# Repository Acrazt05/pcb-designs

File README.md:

# PCB Designs

Circuit boards I designed for my robotics and embedded projects, in KiCad (plus OmniDrone in Altium). All of them were fabricated, assembled, and brought up working.

| Board | Tool | Key parts |
|---|---|---|
| [ESP32-S3 desk robot](#esp32-s3-desk-robot) | KiCad | ESP32-S3-WROOM-1, 1.69" ST7789 SPI LCD, USB-C, buzzer, push buttons, LDO |
| [ESP32-S3 camera board](#esp32-s3-camera-board) | KiCad | ESP32-S3-WROOM-1, 24-pin camera FPC (IMX219-class sensor), 2.8 V / 1.2 V / 3.3 V rails, LED flash driver, DC jack |
| [Brushless actuator controller](#brushless-actuator-controller) | KiCad | ESP32-C3, DRV8305 three-phase gate driver, six IRF40DM229 MOSFETs, TCAN332 CAN transceiver, AS5600 magnetic encoder, LM75B temperature sensor, LMR14206 buck |
| [OmniDrone](#omnidrone) | Altium | ESP-12 (ESP8266), MPU6050 IMU, HMC5883L magnetometer, MS5611 barometer, TP4056 charger |

Each KiCad folder has the design files (`.kicad_pro`, `.kicad_sch`, `.kicad_pcb`), a `schematic.pdf`, and PNG previews in `images/`. Manufacturer datasheets, 3D models, and vendor footprint libraries are not redistributed here; the symbols and footprints are embedded in the KiCad files.

## ESP32-S3 desk robot
A gift desk robot: an ESP32-S3 drives a color LCD face and a buzzer and reads six buttons, powered over USB-C.

## ESP32-S3 camera board
A camera board for robot vision. It carries the extra 2.8 V and 1.2 V rails the image sensor needs, plus a transistor-switched LED flash.

## Brushless actuator controller
A controller for a humanoid-robot joint: an ESP32-C3 drives a brushless motor through a DRV8305 gate driver and a six-MOSFET three-phase bridge, reads rotor angle from an AS5600 magnetic encoder, monitors temperature, and talks to the rest of the robot over CAN. The design is split into a control board and a power bridge board (separate schematic sheets), with the original single-sheet version kept as `source.kicad_sch`.

## OmniDrone
A mini drone whose frame is the circuit board itself, designed in Altium: ESP-12 Wi-Fi flight computer, IMU, magnetometer and barometer, and onboard LiPo charging. See `omnidrone/` for the schematic and board exports.

---
Vinicio Castillo · [GitHub](https://github.com/Acrazt05) · [LinkedIn](https://www.linkedin.com/in/vinicio-castillo) · [Portfolio](https://github.com/Acrazt05/portfolio)

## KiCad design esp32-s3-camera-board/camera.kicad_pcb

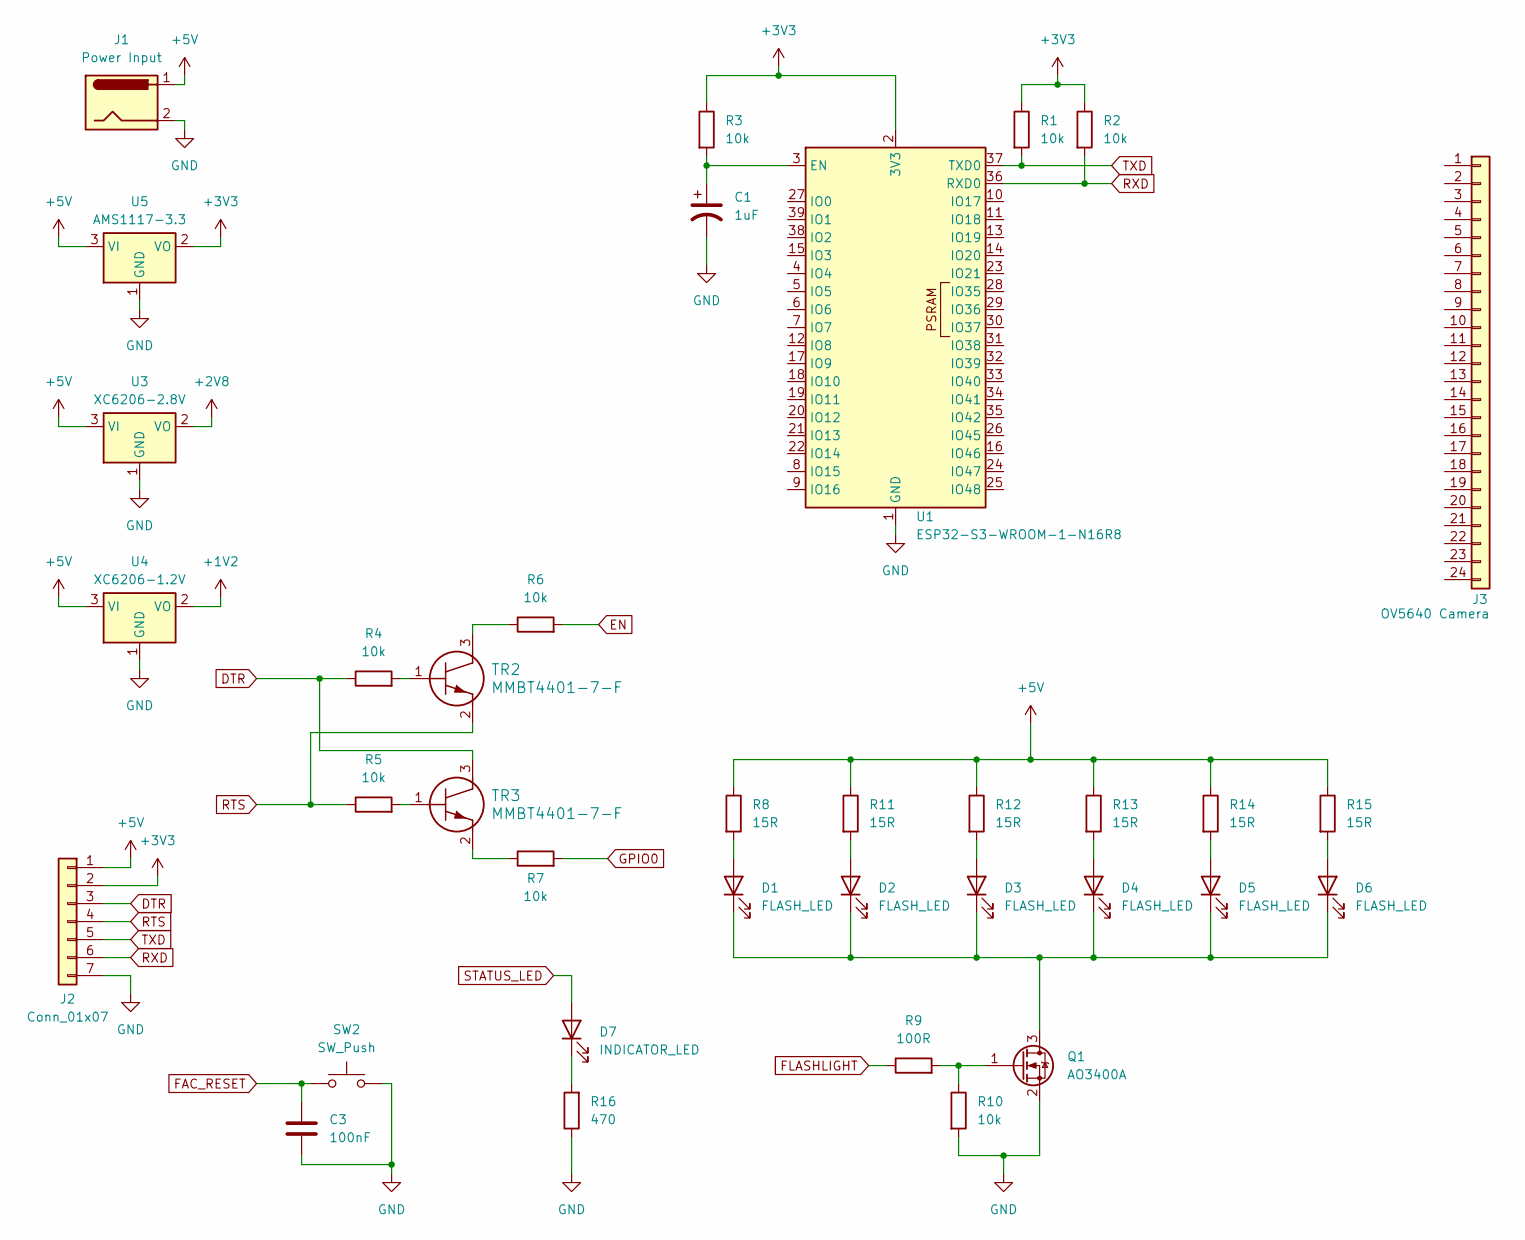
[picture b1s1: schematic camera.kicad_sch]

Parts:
C1: 1uF; CP_Radial_D4.0mm_P2.00mm
C3: 100nF; C_Disc_D5.0mm_W2.5mm_P2.50mm
D1, D2, D3, D4, D5, D6: FLASH_LED; LED_PLCC_2835_Handsoldering
D7: INDICATOR_LED; LED_0603_1608Metric_Pad1.05x0.95mm_HandSolder
J1: Power Input; JACK_ADC-002-x_ADM
J2: Conn_01x07; PinHeader_1x07_P2.54mm_Vertical
J3: OV5640 Camera; XUNPU FPC-05F-24PH20
Q1: AO3400A; SOT-23
R1, R2, R3, R4, R5, R6, R7, R10: 10k; R_1206_3216Metric_Pad1.30x1.75mm_HandSolder
R8, R11, R12, R13, R14, R15: 15R; R_1206_3216Metric_Pad1.30x1.75mm_HandSolder
R9: 100R; R_1206_3216Metric_Pad1.30x1.75mm_HandSolder
R16: 470; R_1206_3216Metric_Pad1.30x1.75mm_HandSolder
SW2: SW_Push; push button 6x6mm 9.5mm height SMD
TR2, TR3: MMBT4401-7-F
U1: ESP32-S3-WROOM-1-N16R8; ESP32-S3-WROOM-1
U3: XC6206-2.8V; SOT-23-3
U4: XC6206-1.2V; SOT-23-3
U5: AMS1117-3.3; SOT-223-3_TabPin2

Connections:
+1V2: U4.2 (VO)
+2V8: U3.2 (VO)
+3V3: J2.2, R1.1, R2.1, R3.1, U1.2 (3V3), U5.2 (VO)
+5V: J1.1, J2.1, R8.1, R11.1, R12.1, R13.1, R14.1, R15.1, U3.3 (VI), U4.3 (VI), U5.3 (VI)
DTR: J2.3, R4.1, TR3.3
EN: R6.2
FAC_RESET: C3.1, SW2.1
FLASHLIGHT: R9.1
GND: C1.2, C3.2, J1.2, J2.7, Q1.2 (S), R10.2, R16.1, SW2.2, U1.1 (GND), U1.40 (GND), U1.41 (GND), U3.1 (GND), U4.1 (GND), U5.1 (GND)
GPIO0: R7.2
unnamed: D1.2 (A), R8.2
unnamed: D1.1 (K), D2.1 (K), D3.1 (K), D4.1 (K), D5.1 (K), D6.1 (K), Q1.3 (D)
unnamed: D2.2 (A), R11.2
unnamed: D3.2 (A), R12.2
unnamed: D4.2 (A), R13.2
unnamed: D5.2 (A), R14.2
unnamed: D6.2 (A), R15.2
unnamed: D7.1 (K), R16.2
unnamed: Q1.1 (G), R9.2, R10.1
unnamed: R4.2, TR2.1
unnamed: R5.2, TR3.1
unnamed: R6.1, TR2.3
unnamed: R7.1, TR3.2
unnamed: C1.1, R3.2, U1.3 (EN)
RTS: J2.4, R5.1, TR2.2
RXD: J2.6, R2.2, U1.36 (RXD0)
STATUS_LED: D7.2 (A)
TXD: J2.5, R1.2, U1.37 (TXD0)

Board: 2 copper layers, 36 parts (0 on the bottom side), 22 nets, no tracks yet.

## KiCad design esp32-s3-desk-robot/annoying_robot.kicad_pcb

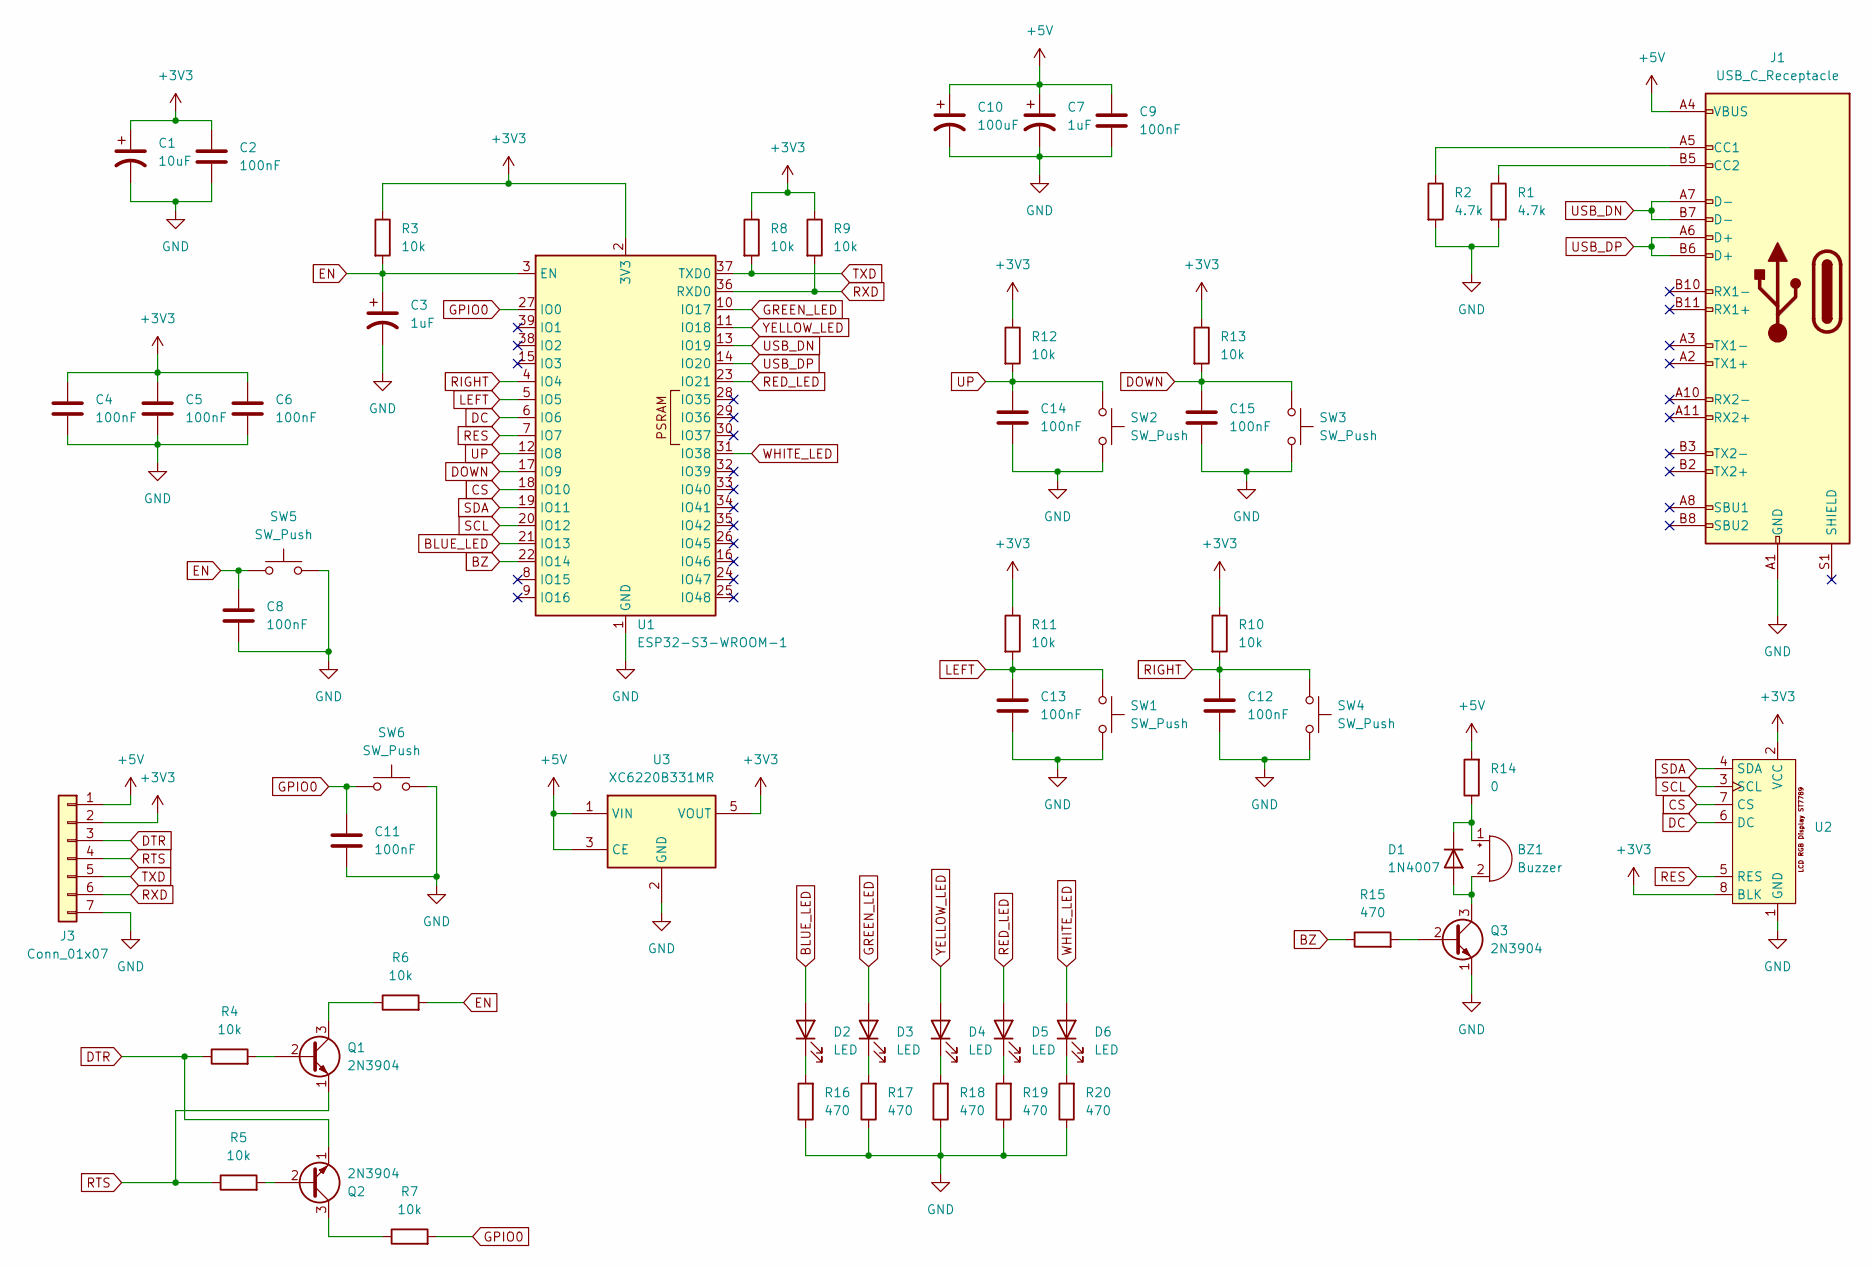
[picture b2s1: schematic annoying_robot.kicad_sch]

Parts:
BZ1: Buzzer; Buzzer_12x9.5RM7.6
C1: 10uF; CP_Radial_D4.0mm_P1.50mm
C2, C4, C5, C6, C8, C9, C11, C12, C13, C14, C15: 100nF; C_Disc_D5.0mm_W2.5mm_P2.50mm
C3, C7: 1uF; CP_Radial_D4.0mm_P2.00mm
C10: 100uF; CP_Radial_D5.0mm_P2.00mm
D1: 1N4007; D_DO-41_SOD81_P10.16mm_Horizontal
D2, D3, D4, D5, D6: LED; LED_D4.0mm
J1: USB_C_Receptacle; USB_C_Receptacle_G-Switch_GT-USB-7010ASV
J3: Conn_01x07; PinHeader_1x07_P2.54mm_Vertical
Q1, Q2, Q3: 2N3904; TO-92
R1, R2: 4.7k; R_1206_3216Metric_Pad1.30x1.75mm_HandSolder
R3, R4, R5, R6, R7, R8, R9, R10, R11, R12, R13: 10k; R_1206_3216Metric_Pad1.30x1.75mm_HandSolder
R14: 0; R_1206_3216Metric_Pad1.30x1.75mm_HandSolder
R15, R16, R17, R18, R19, R20: 470; R_1206_3216Metric_Pad1.30x1.75mm_HandSolder
SW1, SW2, SW3, SW4, SW5, SW6: SW_Push; SW_Push_1P1T_NO_6x6mm_H9.5mm
U1: ESP32-S3-WROOM-1
U2: Screen_1.69_in_240x280_RGB_LCD_3V3_ST7789_SPI_
U3: XC6220B331MR; SOT-23-5

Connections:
+3V3: C1.1, C2.1, C4.1, C5.1, C6.1, J3.2, R3.1, R8.1, R9.1, R10.1, R11.1, R12.1, R13.1, U1.2 (3V3), U2.2 (VCC), U2.8 (BLK), U3.5 (VOUT)
+5V: C7.1, C9.1, C10.1, J1.A4 (VBUS), J1.A9 (VBUS), J1.B4 (VBUS), J1.B9 (VBUS), J3.1, R14.2, U3.1 (VIN), U3.3 (CE)
BLUE_LED: D2.2 (A), U1.21 (IO13)
BZ: R15.1, U1.22 (IO14)
CS: U1.18 (IO10), U2.7 (CS)
DC: U1.6 (IO6), U2.6 (DC)
DOWN: C15.1, R13.2, SW3.1, U1.17 (IO9)
DTR: J3.3, Q2.1 (E), R4.1
EN: C3.1, C8.1, R3.2, R6.2, SW5.1, U1.3 (EN)
GND: C1.2, C2.2, C3.2, C4.2, C5.2, C6.2, C7.2, C8.2, C9.2, C10.2, C11.2, C12.2, C13.2, C14.2, C15.2, J1.A1 (GND), J1.A12 (GND), J1.B1 (GND), J1.B12 (GND), J3.7, Q3.1 (E), R1.2, R2.2, R16.1, R17.1, R18.1, R19.1, R20.1, SW1.2, SW2.2, SW3.2, SW4.2, SW5.2, SW6.2, U1.1 (GND), U1.40 (GND), U1.41 (GND), U2.1 (GND), U3.2 (GND)
GPIO0: C11.1, R7.2, SW6.1, U1.27 (IO0)
GREEN_LED: D3.2 (A), U1.10 (IO17)
LEFT: C13.1, R11.2, SW1.1, U1.5 (IO5)
unnamed: BZ1.1 (+), D1.1 (K), R14.1
unnamed: BZ1.2 (-), D1.2 (A), Q3.3 (C)
unnamed: D2.1 (K), R16.2
unnamed: D3.1 (K), R17.2
unnamed: D4.1 (K), R18.2
unnamed: D5.1 (K), R19.2
unnamed: D6.1 (K), R20.2
unnamed: J1.A5 (CC1), R2.1
unnamed: J1.B5 (CC2), R1.1
unnamed: Q1.2 (B), R4.2
unnamed: Q1.3 (C), R6.1
unnamed: Q2.2 (B), R5.2
unnamed: Q2.3 (C), R7.1
unnamed: Q3.2 (B), R15.2
RED_LED: D5.2 (A), U1.23 (IO21)
RES: U1.7 (IO7), U2.5 (RES)
RIGHT: C12.1, R10.2, SW4.1, U1.4 (IO4)
RTS: J3.4, Q1.1 (E), R5.1
RXD: J3.6, R9.2, U1.36 (RXD0)
SCL: U1.20 (IO12), U2.3 (SCL)
SDA: U1.19 (IO11), U2.4 (SDA)
TXD: J3.5, R8.2, U1.37 (TXD0)
UP: C14.1, R12.2, SW2.1, U1.12 (IO8)
USB_DN: J1.A7 (D-), J1.B7 (D-), U1.13 (IO19)
USB_DP: J1.A6 (D+), J1.B6 (D+), U1.14 (IO20)
WHITE_LED: D6.2 (A), U1.31 (IO38)
YELLOW_LED: D4.2 (A), U1.11 (IO18)

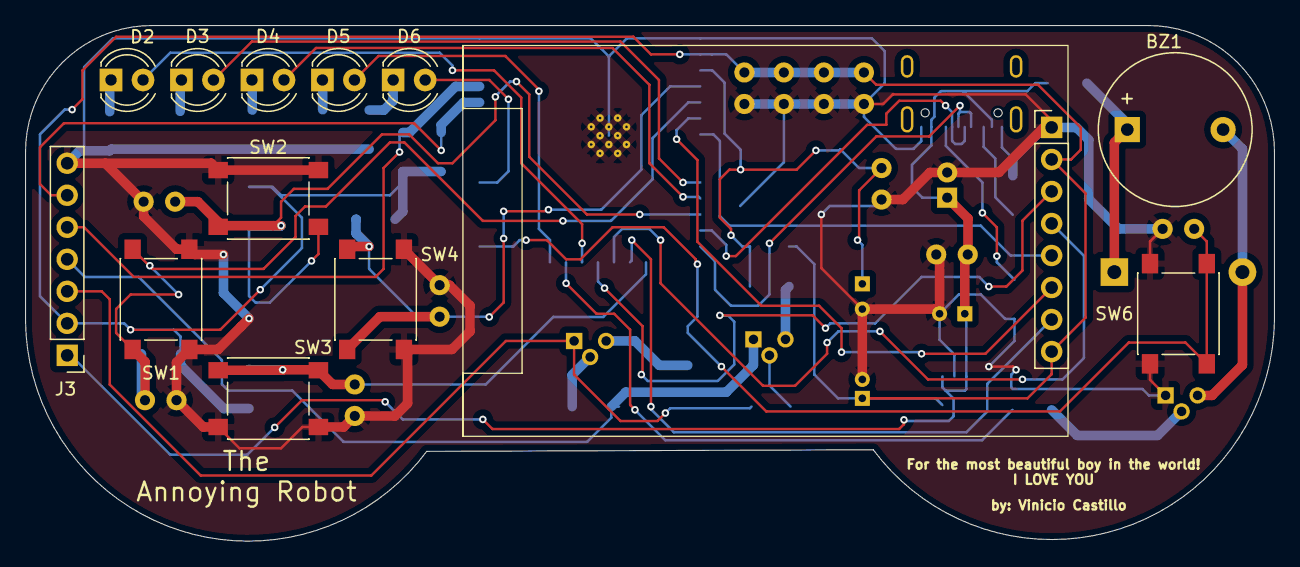
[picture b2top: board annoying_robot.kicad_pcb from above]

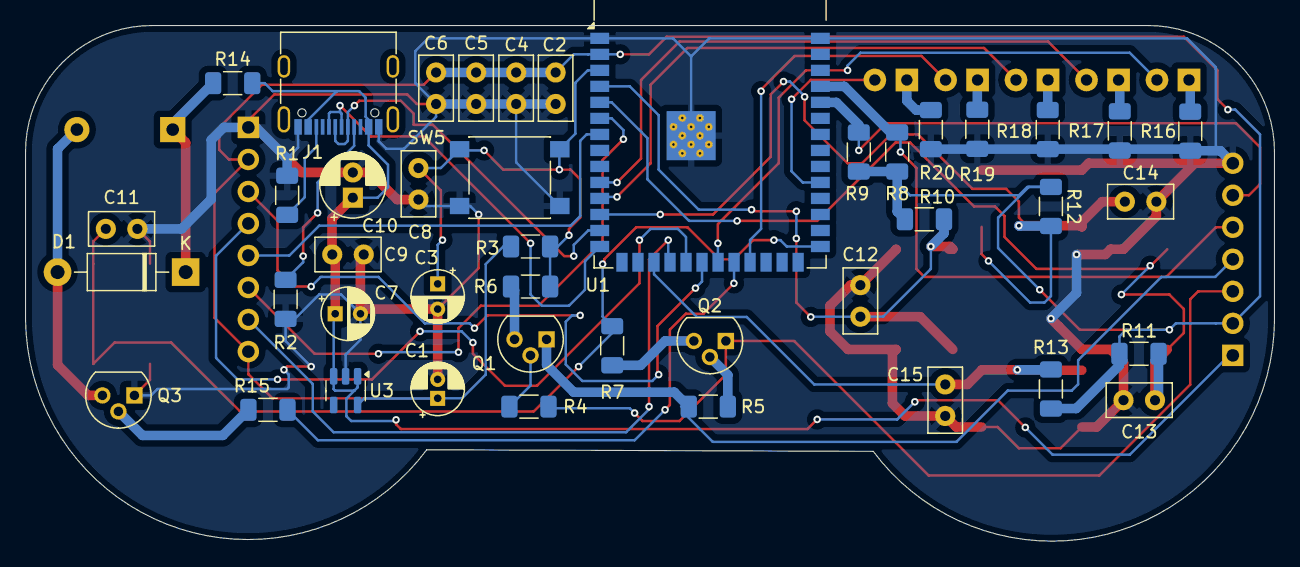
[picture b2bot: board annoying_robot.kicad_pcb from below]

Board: 2 copper layers, 99.1 x 40.9 mm, 56 parts (43 on the bottom side), 40 nets.
